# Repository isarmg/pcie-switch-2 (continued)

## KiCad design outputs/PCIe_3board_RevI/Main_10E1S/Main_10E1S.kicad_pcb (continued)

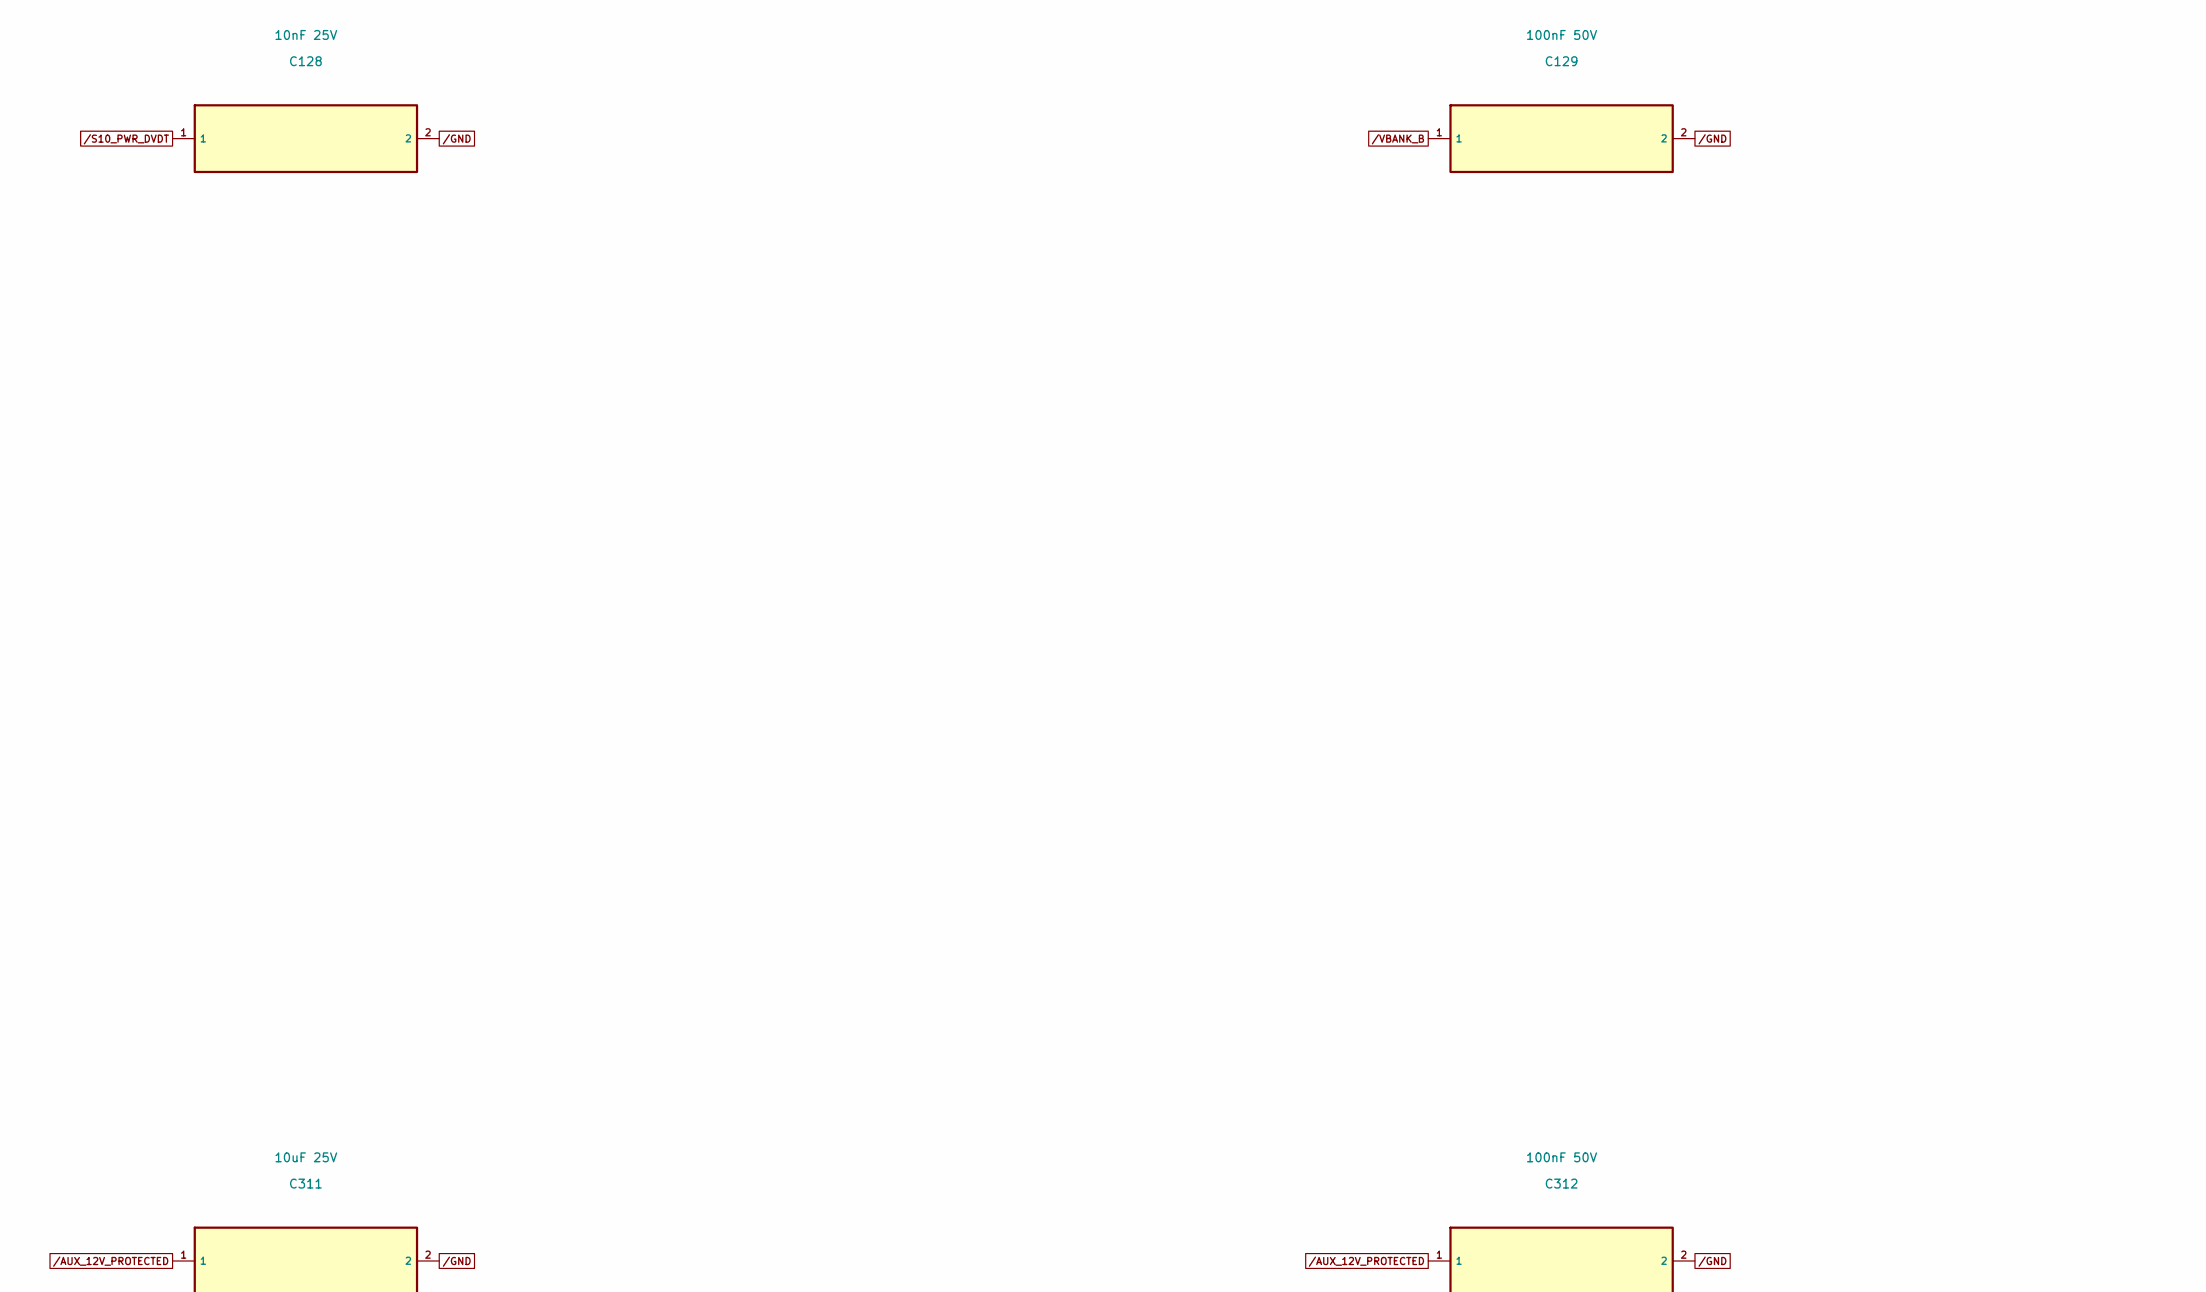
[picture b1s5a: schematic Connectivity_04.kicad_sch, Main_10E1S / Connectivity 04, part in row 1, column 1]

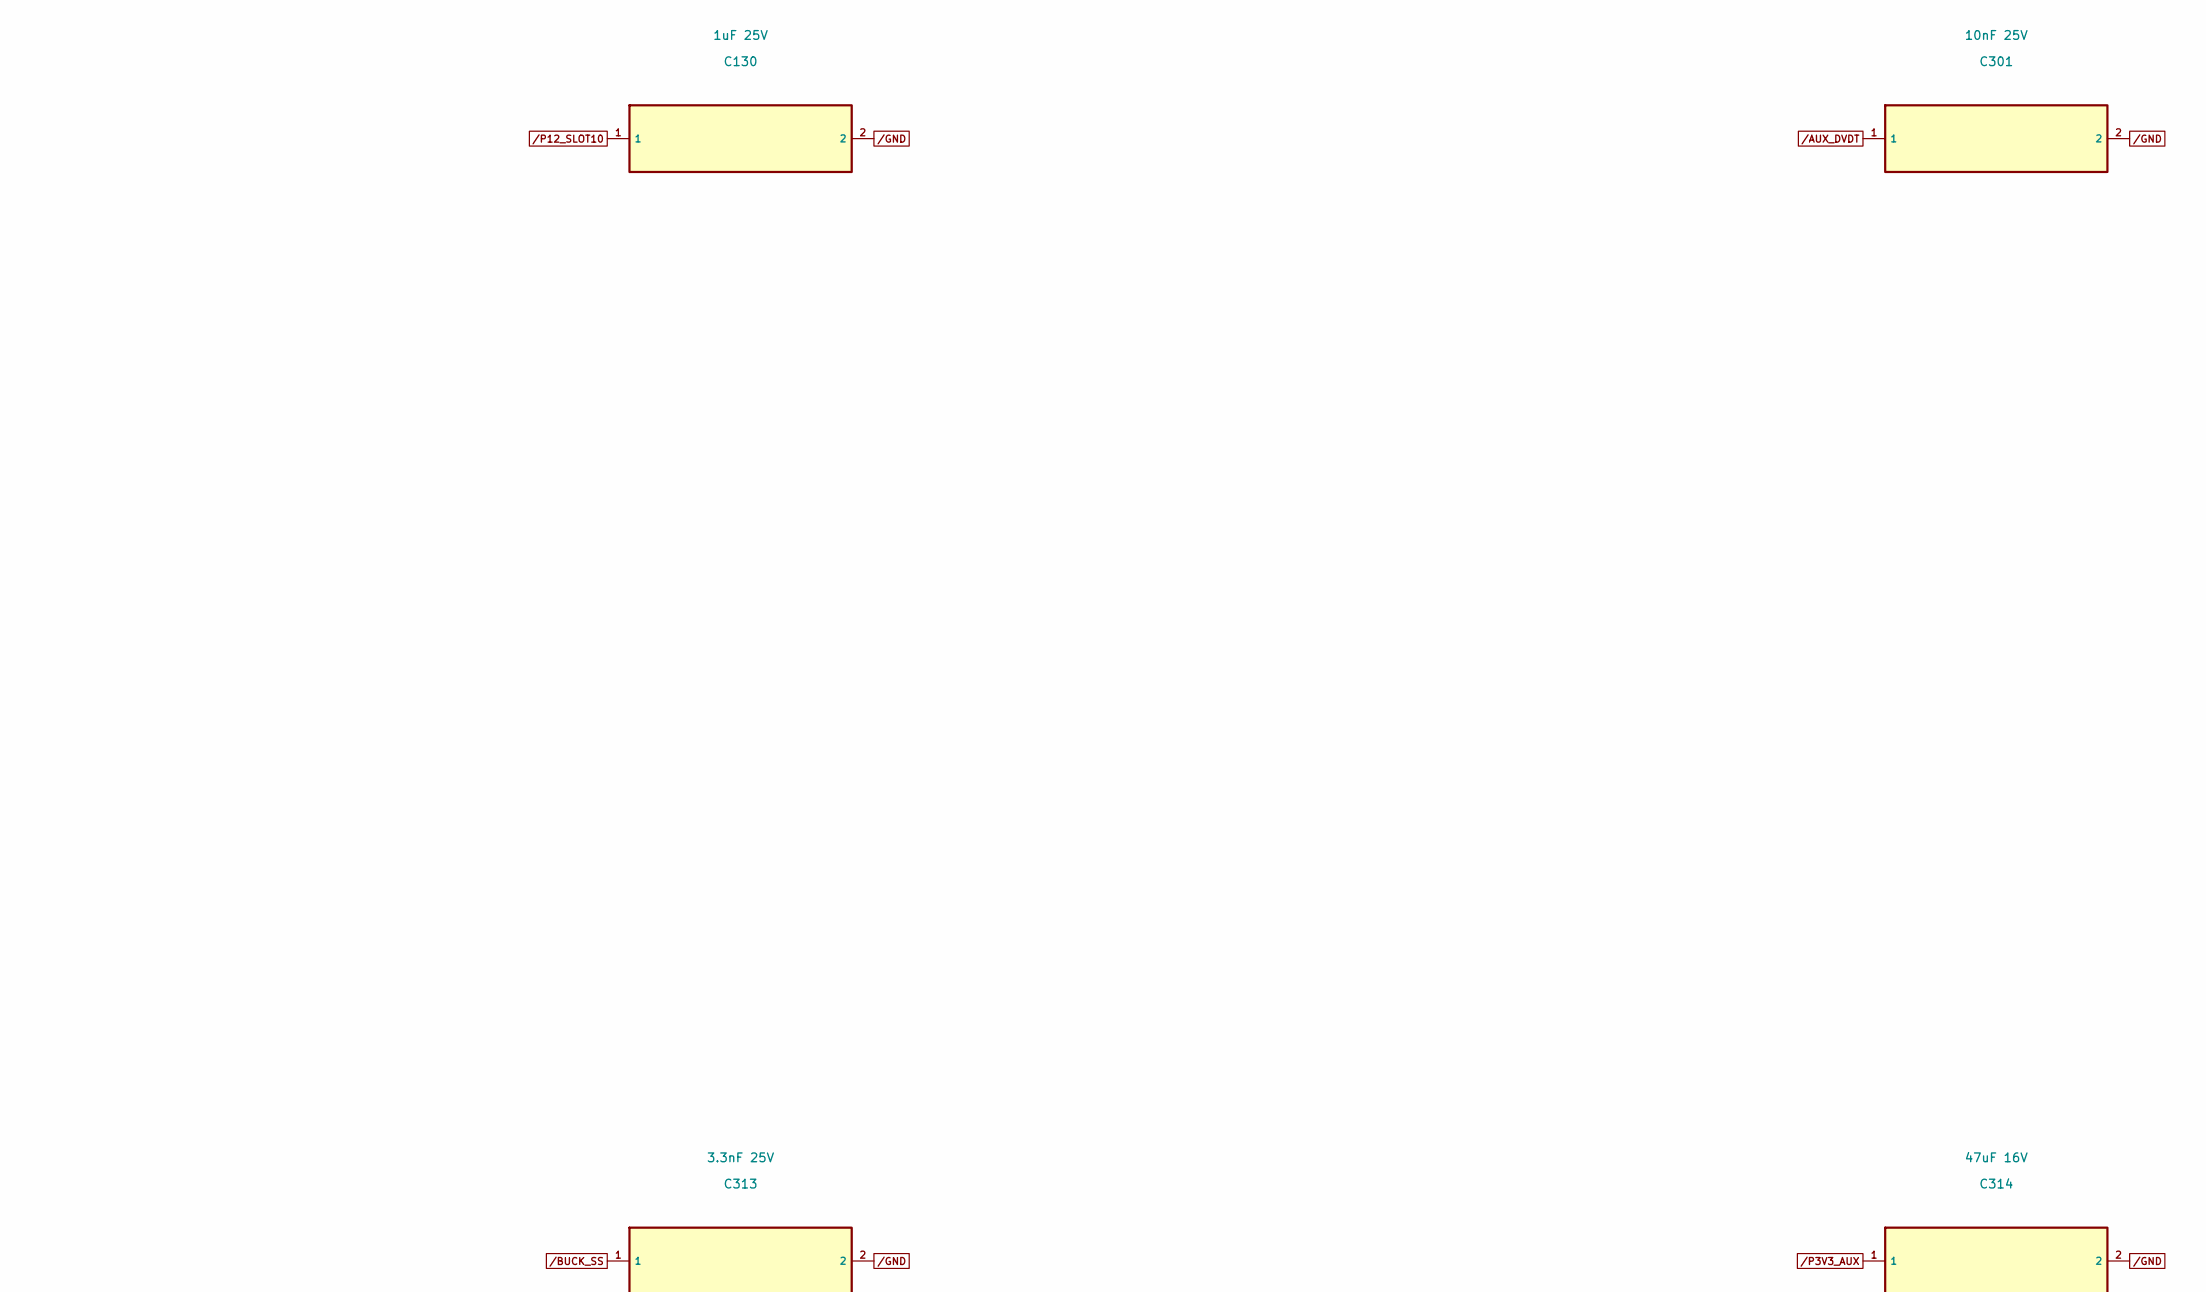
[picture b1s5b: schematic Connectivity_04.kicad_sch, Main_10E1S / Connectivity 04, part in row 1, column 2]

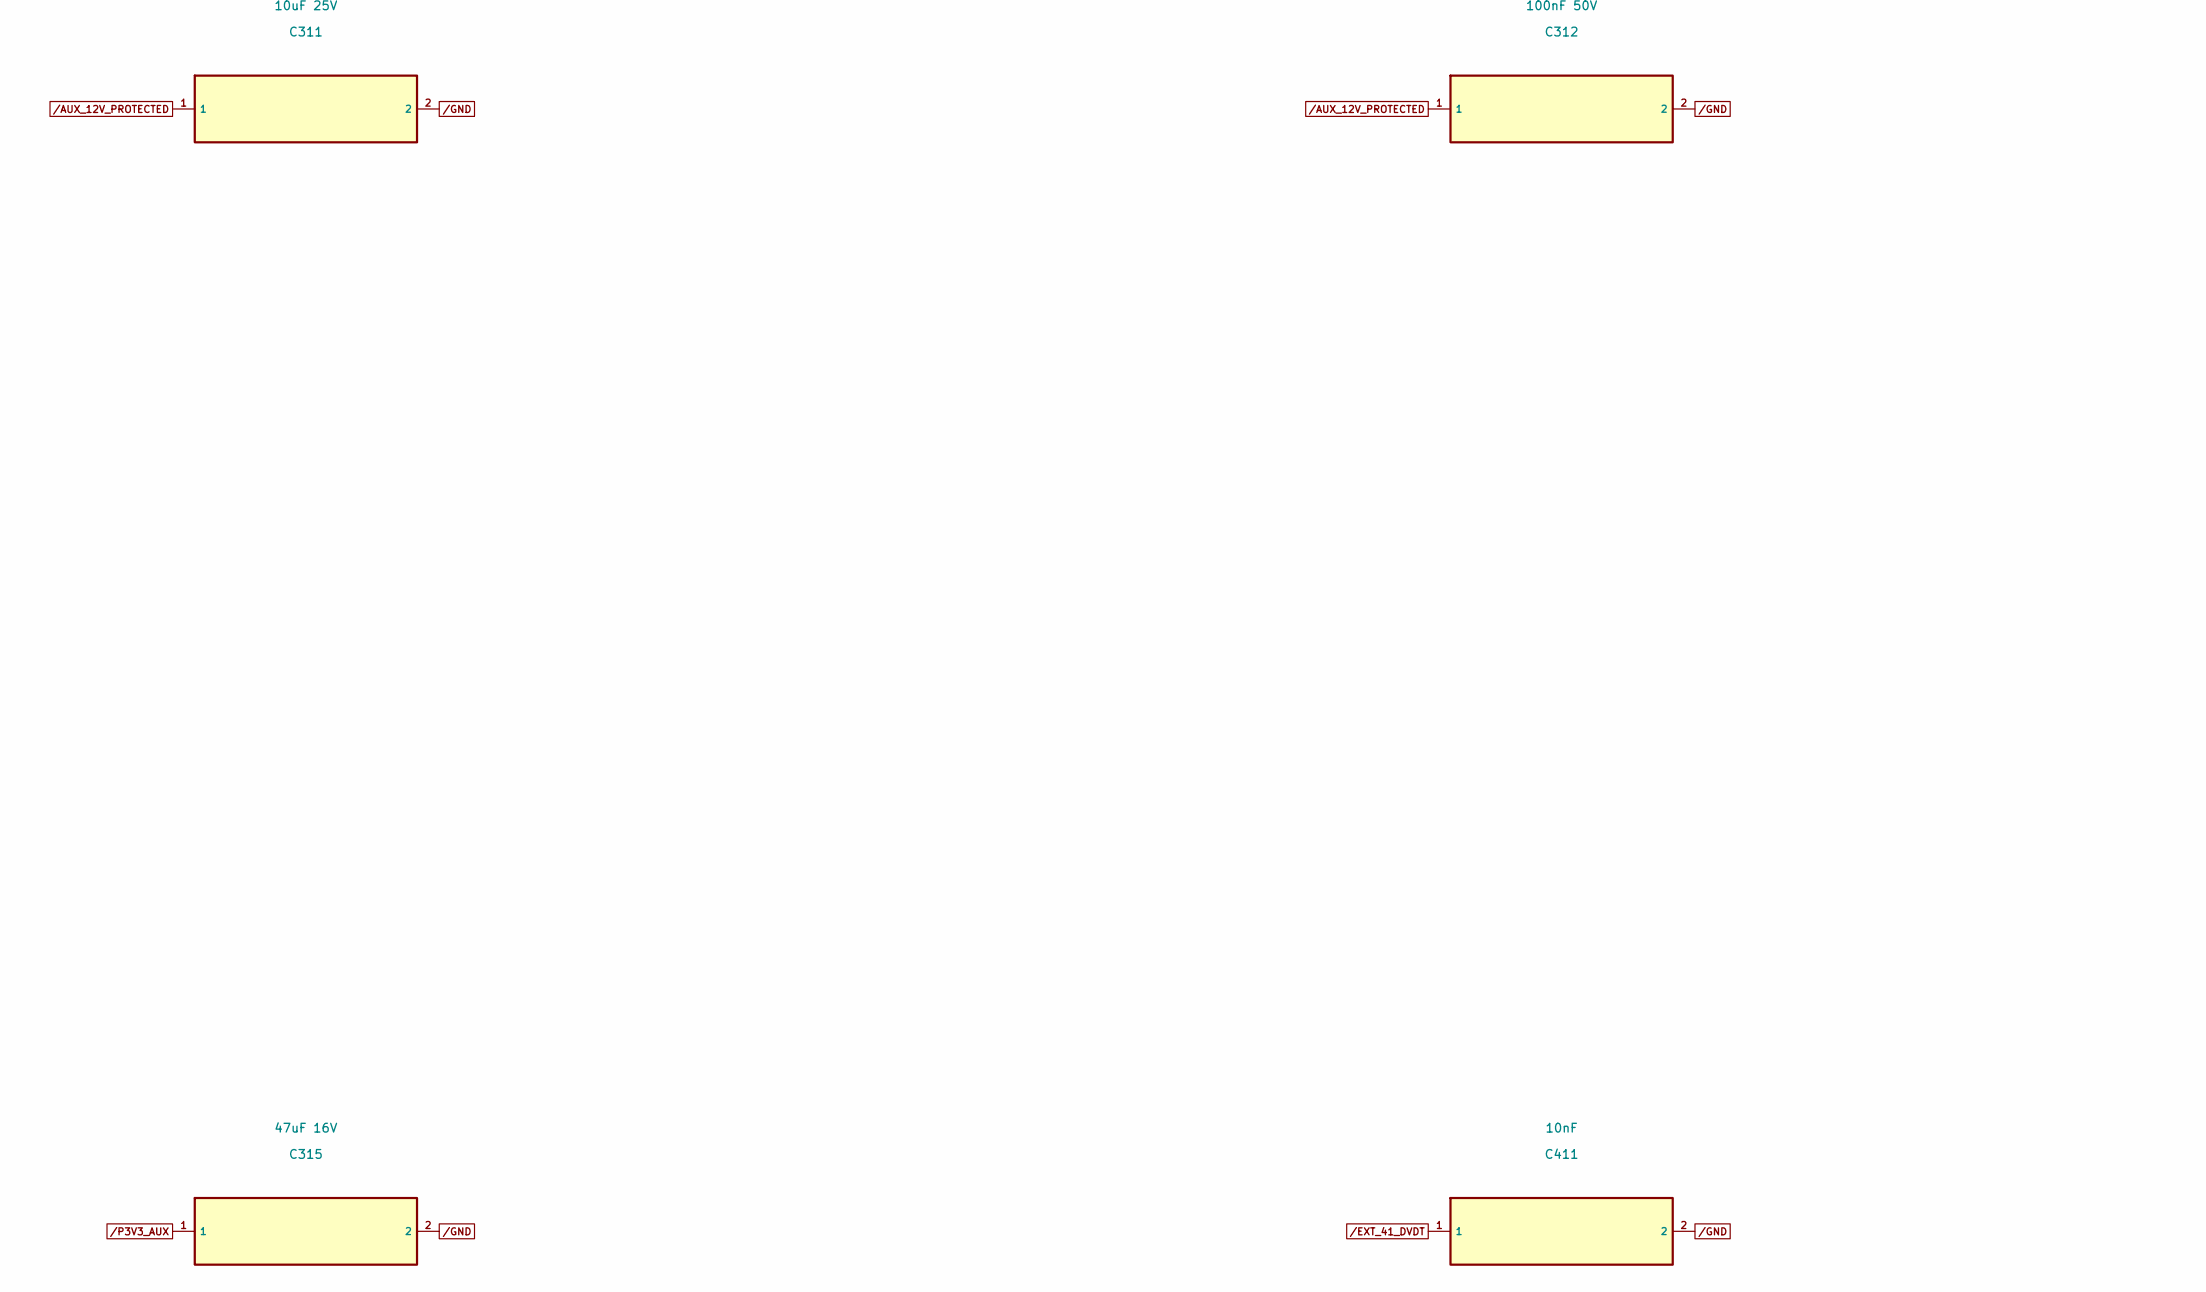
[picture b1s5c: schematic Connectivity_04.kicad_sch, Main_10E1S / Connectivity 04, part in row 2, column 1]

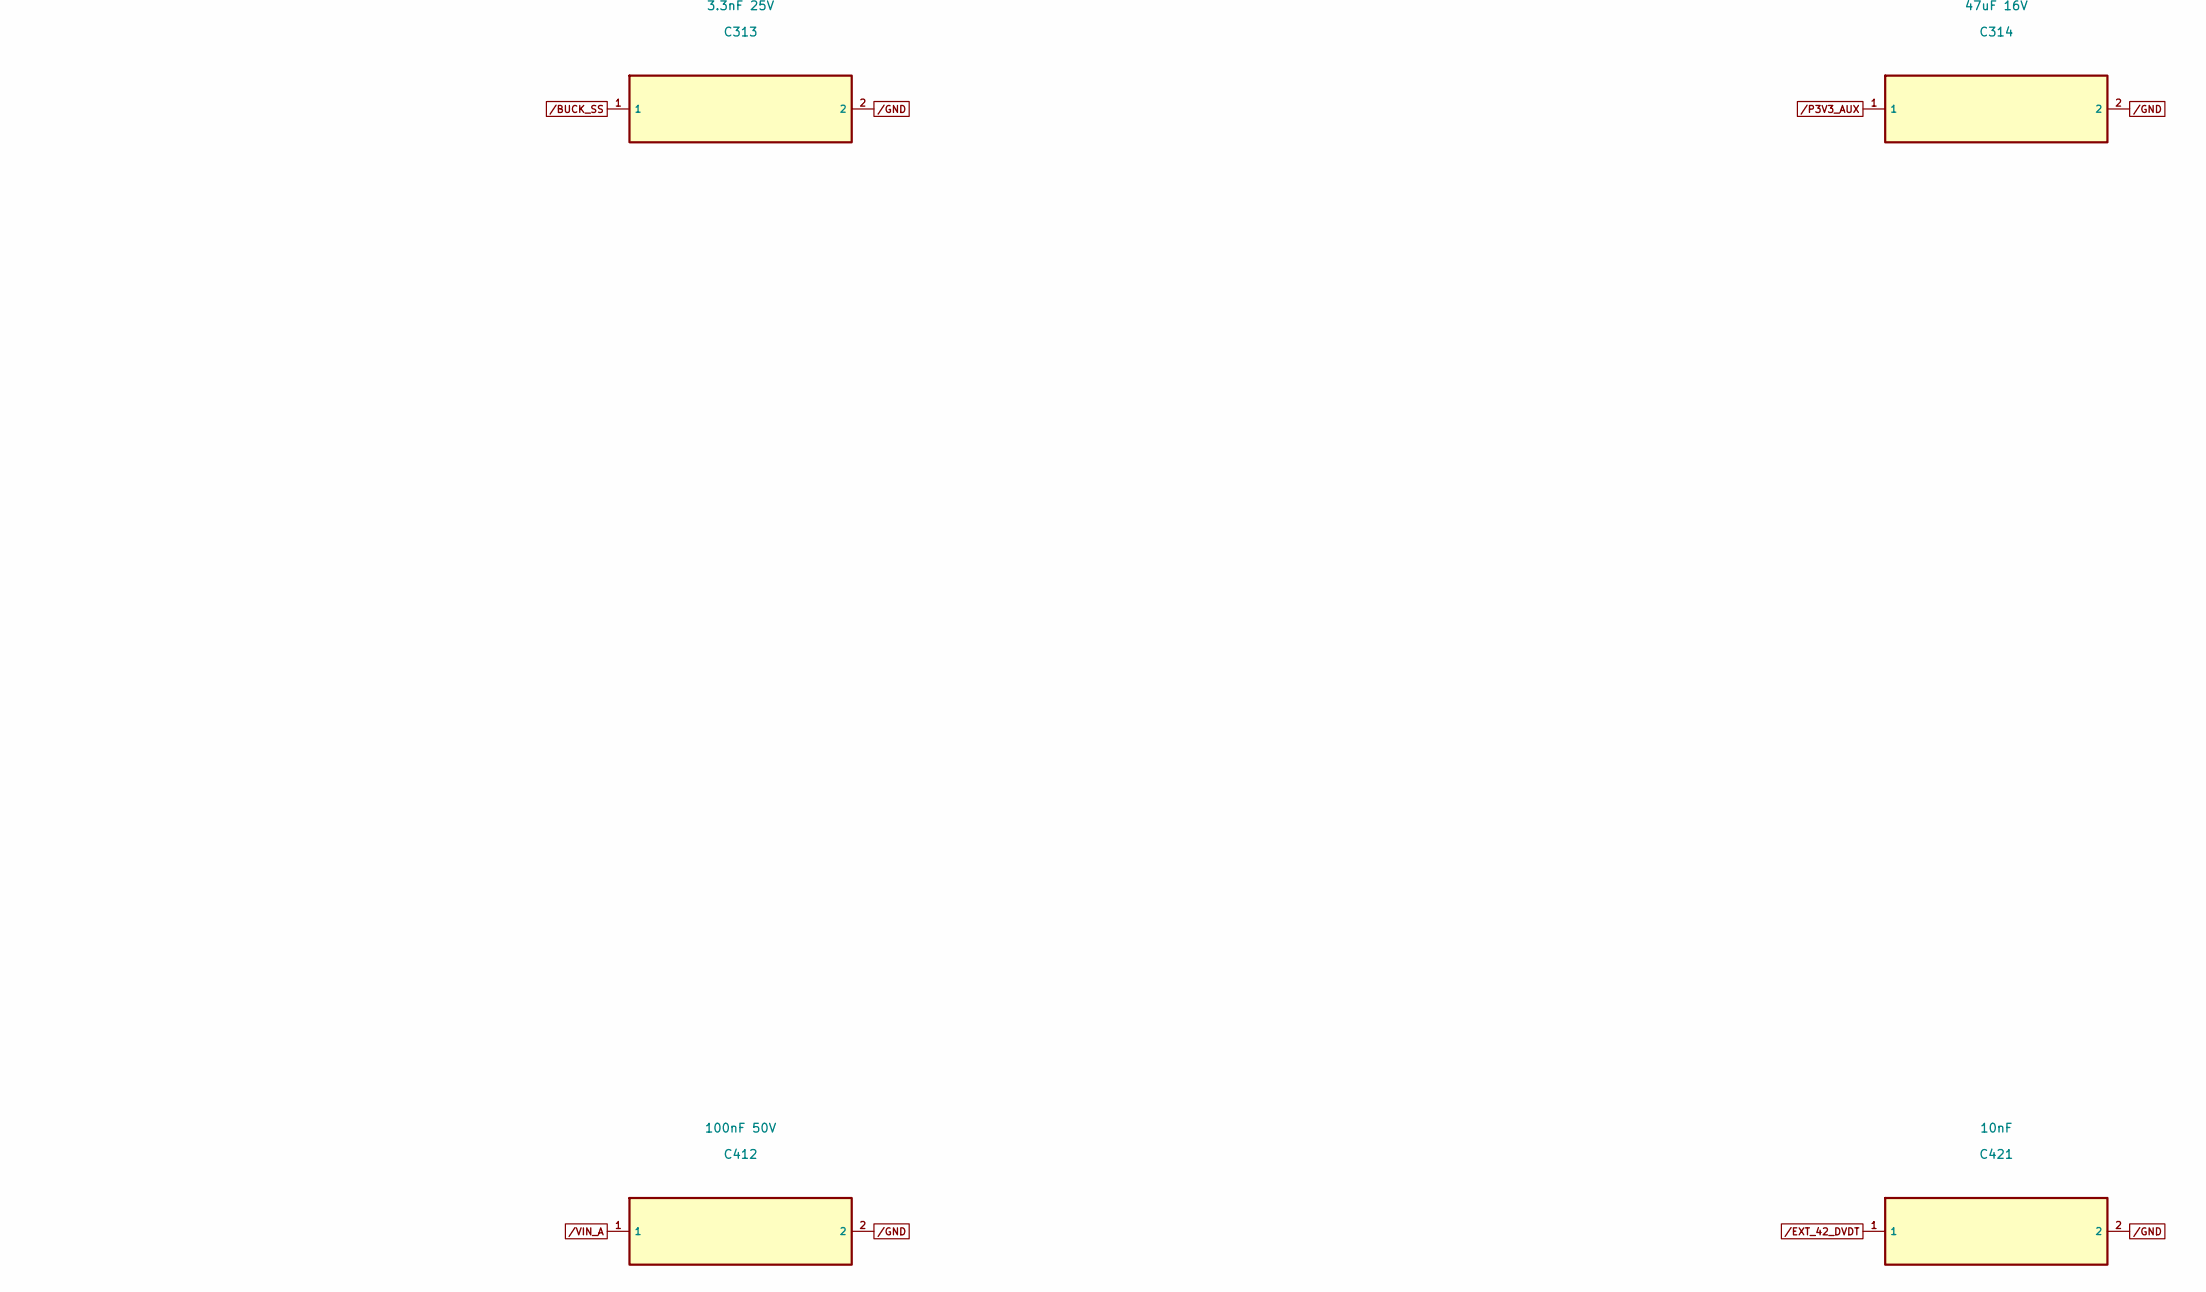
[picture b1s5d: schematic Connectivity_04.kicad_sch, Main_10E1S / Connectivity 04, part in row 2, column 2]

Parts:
C128, C301: 10nF 25V; C_0402_1005Metric
C129, C412: 100nF 50V; C_0603_1608Metric
C130: 1uF 25V; C_0603_1608Metric
C311: 10uF 25V; C_0805_2012Metric
C312: 100nF 50V; C_0402_1005Metric
C313: 3.3nF 25V; C_0402_1005Metric
C314, C315: 47uF 16V; C_1210_3225Metric
C411, C421: 10nF; C_0402_1005Metric

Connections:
/AUX_12V_PROTECTED: C311.1, C312.1; also elsewhere on the board
/AUX_DVDT: C301.1; also elsewhere on the board
/BUCK_SS: C313.1; also elsewhere on the board
/EXT_41_DVDT: C411.1; also elsewhere on the board
/EXT_42_DVDT: C421.1; also elsewhere on the board
/GND: C128.2, C129.2, C130.2, C301.2, C311.2, C312.2, C313.2, C314.2, C315.2, C411.2, C412.2, C421.2; also elsewhere on the board
/P3V3_AUX: C314.1, C315.1; also elsewhere on the board
/P12_SLOT10: C130.1; also elsewhere on the board
/S10_PWR_DVDT: C128.1; also elsewhere on the board
/VBANK_B: C129.1; also elsewhere on the board
/VIN_A: C412.1; also elsewhere on the board
